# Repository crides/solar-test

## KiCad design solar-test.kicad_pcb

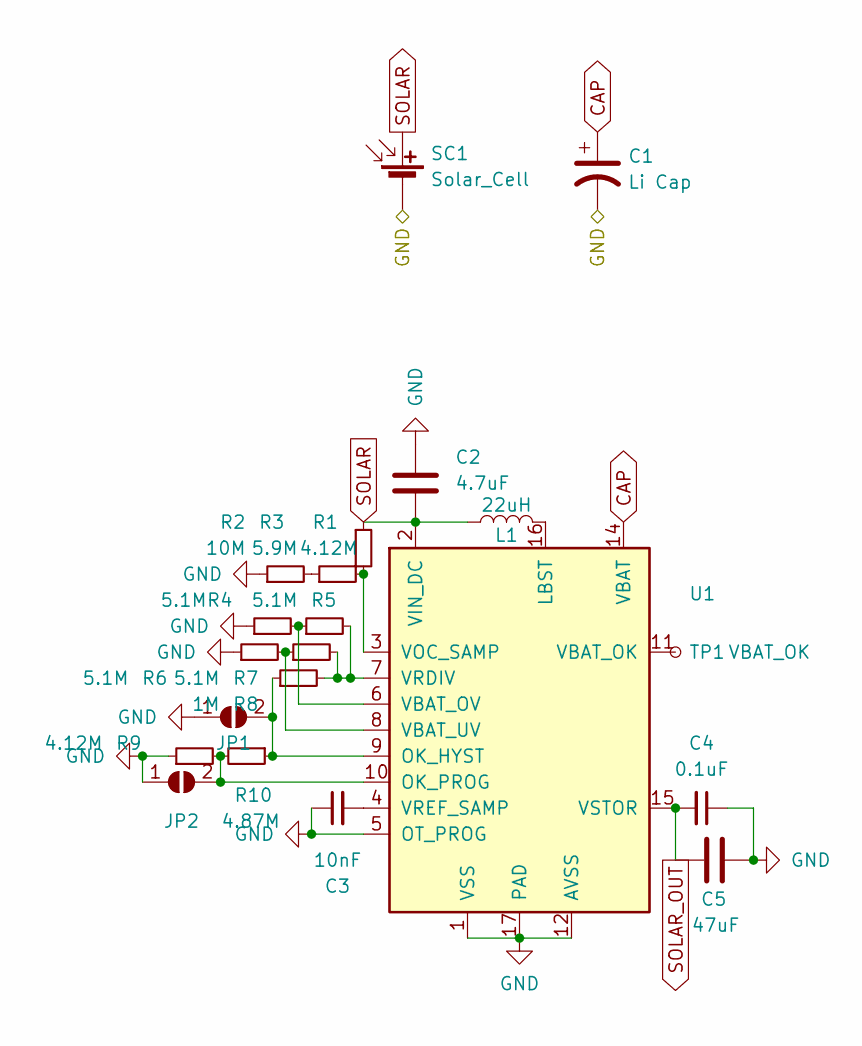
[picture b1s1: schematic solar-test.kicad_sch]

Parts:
C1: Li Cap; CP_Radial_D13.0mm_P5.00mm
C2: 4.7uF; C_0603_1608Metric
C3: 10nF; C_0603_1608Metric
C4: 0.1uF; C_0603_1608Metric
C5: 47uF; C_0805_2012Metric
JP1: SolderJumper-2_P1.3mm_Open_RoundedPad1.0x1.5mm
JP2: SolderJumper_2_Open; SolderJumper-2_P1.3mm_Open_RoundedPad1.0x1.5mm
L1: 22uH; L_Wuerth_WE-TPC-3816
R1, R9: 4.12M; R_0603_1608Metric
R2: 10M; R_0603_1608Metric
R3: 5.9M; R_0603_1608Metric
R4, R5, R6, R7: 5.1M; R_0603_1608Metric
R8: 1M; R_0603_1608Metric
R10: 4.87M; R_0603_1608Metric
SC1: Solar_Cell; KXOB25-05X3F
TP1: VBAT_OK; TestPoint_THTPad_D1.0mm_Drill0.5mm
U1: QFN-16-1EP_3x3mm_P0.5mm_EP1.7x1.7mm

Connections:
CAP: C1.1, U1.14 (VBAT)
GND: C1.2, C2.1, C3.1, C4.1, C5.2, JP1.1 (A), JP2.1 (A), R2.1, R4.1, R6.1, R9.1, SC1.2 (-), U1.1 (VSS), U1.5 (OT_PROG), U1.12 (AVSS), U1.13 (VSS), U1.17 (PAD)
unnamed: C3.2, U1.4 (VREF_SAMP)
unnamed: JP1.2 (B), R8.1, R10.1, U1.9 (OK_HYST)
unnamed: JP2.2 (B), R9.2, R10.2, U1.10 (OK_PROG)
unnamed: L1.2, U1.16 (LBST)
unnamed: R1.2, R3.2, U1.3 (VOC_SAMP)
unnamed: R2.2, R3.1
unnamed: R4.2, R5.1, U1.6 (VBAT_OV)
unnamed: R5.2, R7.2, R8.2, U1.7 (VRDIV)
unnamed: R6.2, R7.1, U1.8 (VBAT_UV)
unnamed: TP1.1, U1.11 (VBAT_OK)
SOLAR: C2.2, L1.1, R1.1, SC1.1 (+), U1.2 (VIN_DC)
SOLAR_OUT: C4.2, C5.1, U1.15 (VSTOR)

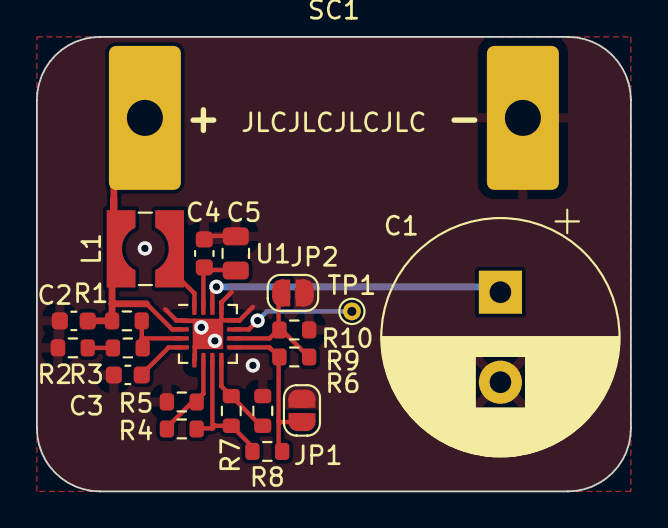
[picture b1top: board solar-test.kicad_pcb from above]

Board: 2 copper layers, 33.0 x 25.2 mm, 21 parts (0 on the bottom side), 14 nets.

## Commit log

2023-07-12 backup
